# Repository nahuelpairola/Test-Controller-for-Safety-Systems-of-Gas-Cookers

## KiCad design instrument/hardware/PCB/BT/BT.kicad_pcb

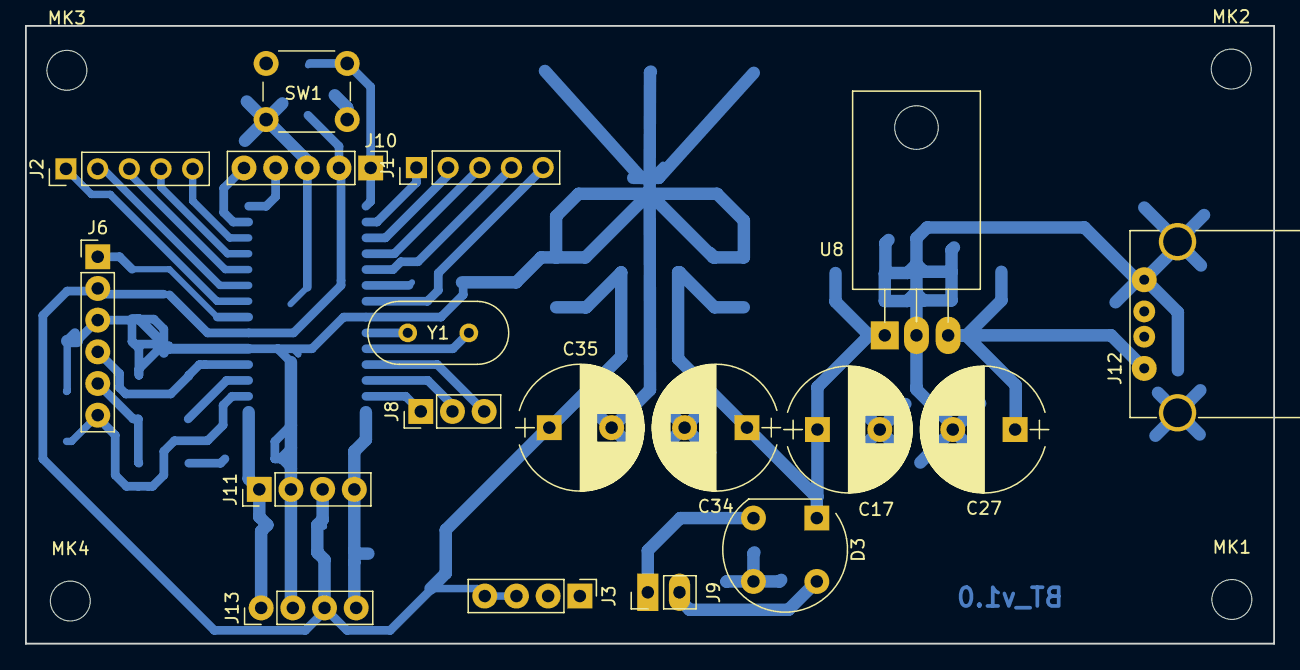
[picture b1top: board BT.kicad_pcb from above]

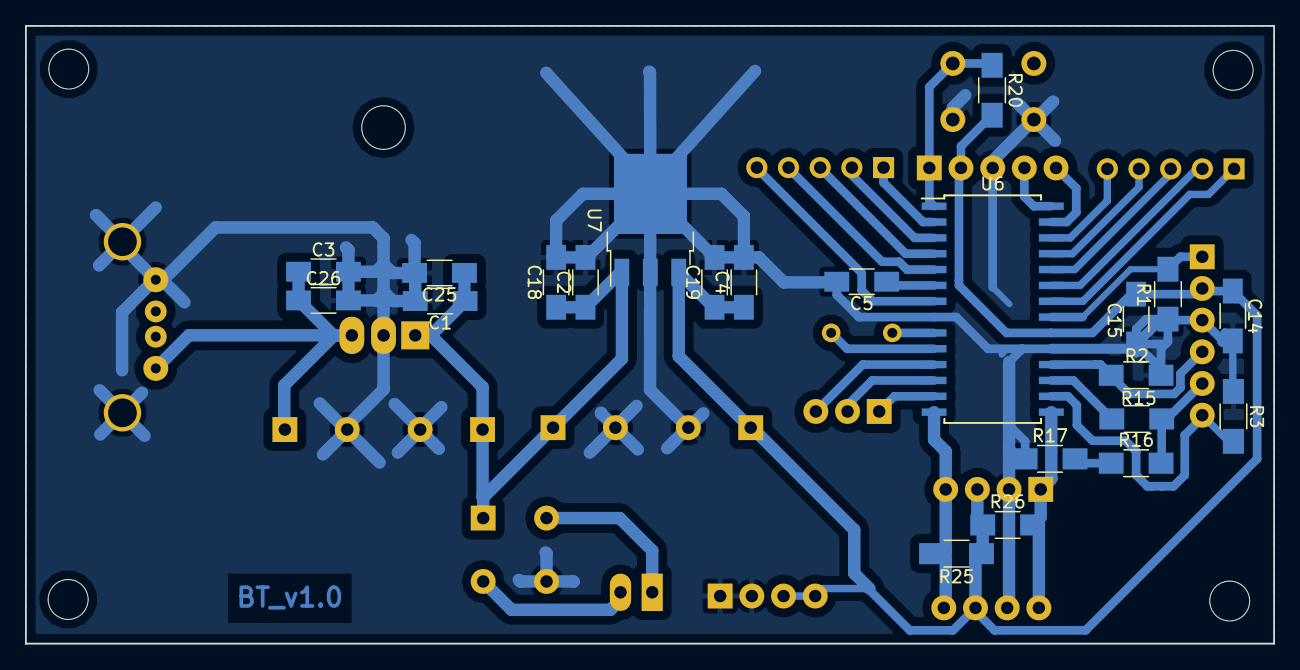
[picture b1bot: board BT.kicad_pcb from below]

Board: 2 copper layers, 100.1 x 49.5 mm, 44 parts (22 on the bottom side), 33 nets.

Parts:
C1, C2, C19, C26: 1nF; C_1206_HandSoldering
C3, C4, C5, C14, C15, C18, C25: 10nF; C_1206_HandSoldering
C17, C27, C34, C35: 1000uF; CP_Radial_D10.0mm_P5.00mm
D3: D_Bridge_+A-A; Diode_Bridge_Round_D9.8mm
J1: CONN_LED_2; Pin_Header_Straight_1x05_Pitch2.54mm
J2: CONN_LED_1; Pin_Header_Straight_1x05_Pitch2.54mm
J3: CONN_PWR_FREE; Pin_Header_Straight_1x04_Pitch2.54mm
J6: CONN_UC_HC05; Socket_Strip_Straight_1x06_Pitch2.54mm
J8: CONN_UC_FREE_3; Pin_Header_Straight_1x03_Pitch2.54mm
J9: CONN_UC_PWR_INPUT; Pin_Header_Straight_1x02_Pitch2.54mm
J10: CONN_UC_ICSP; Pin_Header_Straight_1x05_Pitch2.54mm
J11: CONN_ADQ_1; Pin_Header_Straight_1x04_Pitch2.54mm
J12: USB; USB_A
J13: CONN_ADQ_2; Pin_Header_Straight_1x04_Pitch2.54mm
MK1, MK2, MK3, MK4: Mounting_Hole; MountingHole_3.2mm_M3
R1, R2, R3, R15, R16, R17, R20, R25, R26: 22k; R_1206_HandSoldering
SW1: SW_Reset; SW_PUSH_6mm
U6: PIC18F25K80_I/SS; SOIC-28W_7.5x17.9mm_Pitch1.27mm
U7: L7805; TO-252-3_TabPin2
U8: 7805; TO-220_Horizontal
Y1: Crystal; Crystal_HC18-U_Vertical

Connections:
+5V: C4.1, C14.1, C15.1, C19.1, C35.1, J3.3, J3.4, J6.2, J10.2, J11.3, J13.3, R20.2, R25.1, R26.1, U6.20, U7.3
EN: J6.1, R1.1, U6.21
GND: C1.2, C2.2, C3.2, C4.2, C5.2, C14.2, C15.2, C17.2, C18.2, C19.2, C25.2, C26.2, C27.2, C34.2, C35.2, D3.3, J3.1, J3.2, J6.3, J10.3, J11.2, J12.4, J12.5, J13.2, R1.2, R2.1, R3.1, R17.1, SW1.1, U6.8, U6.19, U7.2, U8.2
HC05_RX: R15.2, U6.17
HC05_TX: J6.4, R2.2, U6.18
unnamed: C1.1, C2.1, C17.1, C18.1, C25.1, C34.1, D3.1, U7.1, U8.1
unnamed: C5.1, U6.6
unnamed: C3.1, C26.1, C27.1, J12.1, U8.3
unnamed: D3.2, J9.1
unnamed: D3.4, J9.2
unnamed: J1.1, U6.2
unnamed: J1.2, U6.3
unnamed: J1.3, U6.4
unnamed: J1.4, U6.5
unnamed: J1.5, U6.7
unnamed: J2.1, U6.22
unnamed: J2.2, U6.23
unnamed: J2.3, U6.24
unnamed: J2.4, U6.25
unnamed: J2.5, U6.26
unnamed: J6.5, R15.1, R16.2
unnamed: J8.1, U6.13
unnamed: J8.2, U6.12
unnamed: J8.3, U6.11
unnamed: R16.1, R17.2
unnamed: U6.9, Y1.1
unnamed: U6.10, Y1.2
PGC: J10.5, U6.27
PGD: J10.4, U6.28
STATE: J6.6, R3.2, U6.16
UC_SCL: J11.4, J13.4, R25.2, U6.14
UC_SDA: J11.1, J13.1, R26.2, U6.15
~MCLR: J10.1, R20.1, SW1.2, U6.1
